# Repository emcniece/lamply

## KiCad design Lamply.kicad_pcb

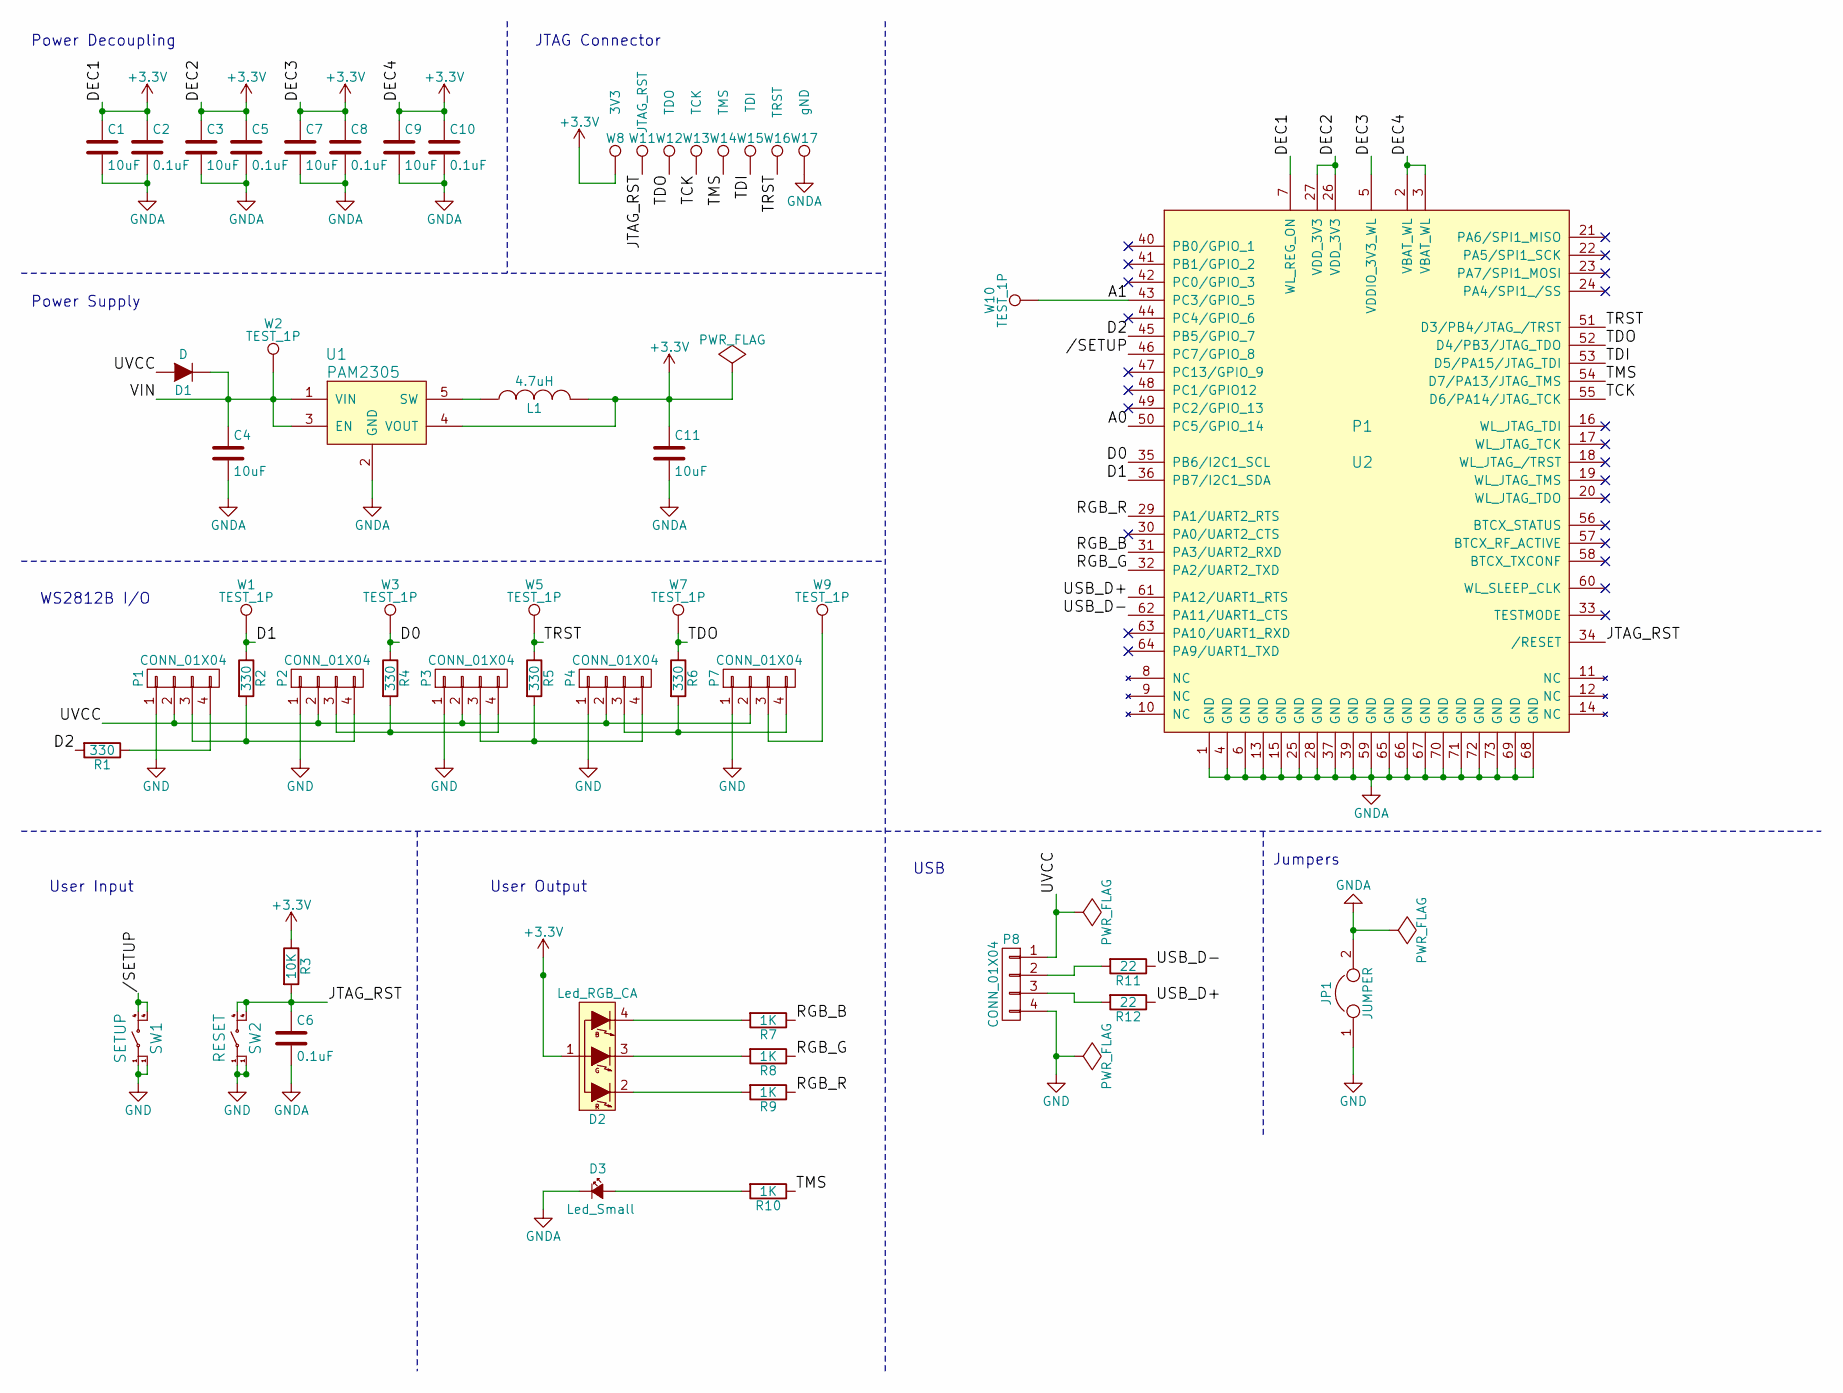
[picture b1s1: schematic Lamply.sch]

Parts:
C1, C3, C4, C7, C9, C11: 10uF; C_0805_HandSoldering
C2, C5, C6, C8, C10: 0.1uF; C_0805_HandSoldering
D1: D; DO-220AA
D2: Led_RGB_CA; CLMVB-FKA
D3: Led_Small; LED_0805
JP1: JUMPER; NetTie-I
L1: 4.7uH; C_0603_HandSoldering
P1, P2, P3, P4, P7, P8: CONN_01X04; JST_B4B-XH-A
R1, R2, R4, R5, R6: 330; R_0805_HandSoldering
R3: 10K; R_0805_HandSoldering
R7, R8, R9, R10: 1K; R_0805_HandSoldering
R11, R12: 22; R_0805_HandSoldering
SW1: SETUP; PTS645
SW2: RESET; PTS645
U1: PAM2305; SOT-23-5
U2: P1; p1
W1, W2, W3, W5, W7, W9, W10: TEST_1P; Measurement_Point_Square-SMD-Pad_Small
W8: 3V3; Measurement_Point_Square-SMD-Pad_Small
W11: JTAG_RST; Measurement_Point_Square-SMD-Pad_Small
W12: TDO; Measurement_Point_Square-SMD-Pad_Small
W13: TCK; Measurement_Point_Square-SMD-Pad_Small
W14: TMS; Measurement_Point_Square-SMD-Pad_Small
W15: TDI; Measurement_Point_Square-SMD-Pad_Small
W16: TRST; Measurement_Point_Square-SMD-Pad_Small
W17: gND; Measurement_Point_Square-SMD-Pad_Small

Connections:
+3V3: C1.1, C2.1, C3.1, C5.1, C7.1, C8.1, C9.1, C10.1, C11.1, D2.1, L1.2, R3.1, U1.4 (VOUT), U2.2 (VBAT_WL), U2.3 (VBAT_WL), U2.5 (VDDIO_3V3_WL), U2.7 (WL_REG_ON), U2.26 (VDD_3V3), U2.27 (VDD_3V3), W8.1
//SETUP: SW1.4, U2.46 (PC7/GPIO_8)
/A0: U2.50 (PC5/GPIO_14)
/A1: U2.43 (PC3/GPIO_5), W10.1
/D0: R4.1, U2.35 (PB6/I2C1_SCL), W3.1
/D1: R2.1, U2.36 (PB7/I2C1_SDA), W1.1
/D2: R1.2, U2.45 (PB5/GPIO_7)
/JTAG_RST: C6.1, R3.2, SW2.4, U2.34 (/RESET), W11.1
/RGB_B: R7.1, U2.31 (PA3/UART2_RXD)
/RGB_G: R8.1, U2.32 (PA2/UART2_TXD)
/RGB_R: R9.1, U2.29 (PA1/UART2_RTS)
/TCK: U2.55 (D6/PA14/JTAG_TCK), W13.1
/TDI: U2.53 (D5/PA15/JTAG_TDI), W15.1
/TDO: R6.1, U2.52 (D4/PB3/JTAG_TDO), W7.1, W12.1
/TMS: R10.1, U2.54 (D7/PA13/JTAG_TMS), W14.1
/TRST: R5.1, U2.51 (D3/PB4/JTAG_/TRST), W5.1, W16.1
/USB_D+: R12.1, U2.61 (PA12/UART1_RTS)
/USB_D-: R11.1, U2.62 (PA11/UART1_CTS)
/UVCC: D1.2 (A), P1.2, P2.2, P3.2, P4.2, P7.2, P8.1
/VIN: C4.1, D1.1 (K), U1.1 (VIN), U1.3 (EN), W2.1
GND: JP1.1, P1.1, P2.1, P3.1, P4.1, P7.1, P8.4, SW1.1, SW2.1
GNDA: C1.2, C2.2, C3.2, C4.2, C5.2, C6.2, C7.2, C8.2, C9.2, C10.2, C11.2, D3.1 (K), JP1.2, U1.2 (GND), U2.1 (GND), U2.4 (GND), U2.6 (GND), U2.13 (GND), U2.15 (GND), U2.25 (GND), U2.28 (GND), U2.37 (GND), U2.39 (GND), U2.59 (GND), U2.65 (GND), U2.66 (GND), U2.67 (GND), U2.68 (GND), U2.69 (GND), U2.70 (GND), U2.71 (GND), U2.72 (GND), U2.73 (GND), W17.1
unnamed: D2.2 (R), R9.2
unnamed: D2.3 (G), R8.2
unnamed: D2.4 (B), R7.2
unnamed: D3.2 (A), R10.2
unnamed: L1.1, U1.5 (SW)
unnamed: P1.3, P2.4, R2.2
unnamed: P1.4, R1.1
unnamed: P2.3, P3.4, R4.2
unnamed: P3.3, P4.4, R5.2
unnamed: P4.3, P7.4, R6.2
unnamed: P7.3, W9.1
unnamed: P8.2, R11.2
unnamed: P8.3, R12.2

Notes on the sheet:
Power Decoupling
JTAG Connector
Power Supply
WS2812B I/O
User Input
User Output
USB
Jumpers

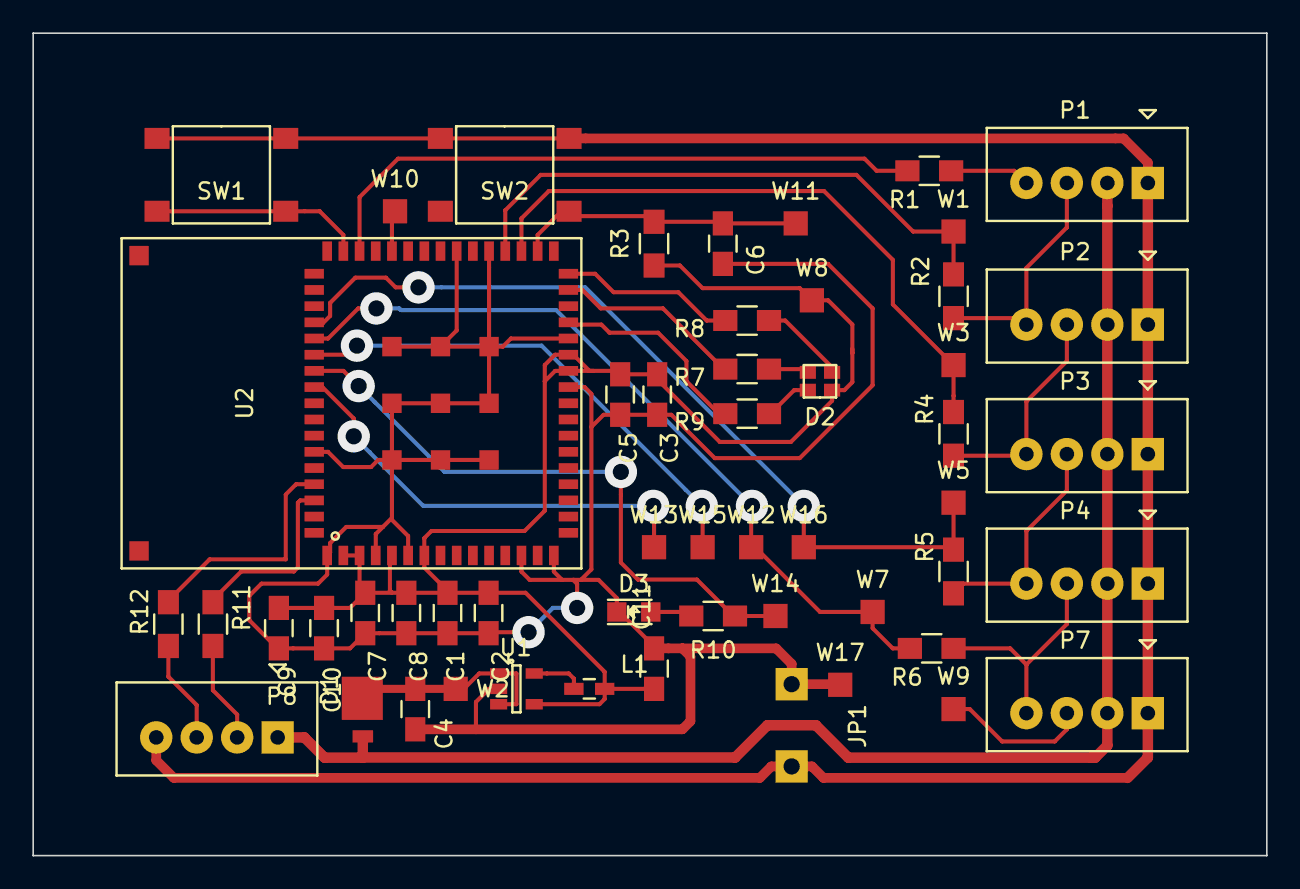
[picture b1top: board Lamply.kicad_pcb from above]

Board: 2 copper layers, 76.2 x 50.8 mm, 53 parts (0 on the bottom side), 34 nets.

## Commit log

2016-08-25 Converting to Kicad
2016-08-26 Simon overhaul assist
2016-08-30 Enlarging via drills
2016-09-01 Enlarging vias
2016-09-01 Generated drill file
2016-09-13 Fixing PTH and vias
